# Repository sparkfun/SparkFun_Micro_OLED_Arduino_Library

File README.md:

SparkFun Micro OLED Breakout Arduino Library
========================================

<table class="table table-hover table-striped table-bordered">
  <tr align="center">
   <td></td>
   <td></td>
  </tr>
  <tr align="center">
    <td><i><a href="https://www.sparkfun.com/products/13003">SparkFun Micro OLED Breakout (LCD-13003)</a></i></td>
    <td><i><a href="https://www.sparkfun.com/products/14532">SparkFun Micro OLED Breakout (Qwiic)</a></i></td>
  </tr>
</table>

An Arduino library that allows you to draw shapes and text on the Micro OLED display and Qwiic micro OLED breakout.

Repository Contents
-------------------

* **/examples** - Example sketches for the library (.ino). Run these from the Arduino IDE.
* **/src** - Source files for the library (.cpp, .h).
* **keywords.txt** - Keywords from this library that will be highlighted in the Arduino IDE.
* **library.properties** - General library properties for the Arduino package manager.

Documentation
--------------

* **[Installing an Arduino Library Guide](https://learn.sparkfun.com/tutorials/installing-an-arduino-library)** - Basic information on how to install an Arduino library.
* **[Product Repository](https://github.com/sparkfun/Micro_OLED_Breakout)** - Main repository (including hardware files) for the Micro OLED Breakout.
* **[Hookup Guide](https://learn.sparkfun.com/tutorials/micro-oled-breakout-hookup-guide)** - Hookup guide for the Micro OLED Breakout.
* **[Hookup Guide (Qwiic version)](https://learn.sparkfun.com/tutorials/718)** - Hookup guide for the Micro OLED Breakout (Qwiic).

Products that use this Library
---------------------------------

* [Micro OLED Breakout](https://www.sparkfun.com/products/13003)- A breakout for the monochrome 64x48 OLED.
* [Micro OLED Breakout (Qwiic)](https://www.sparkfun.com/products/14532) - Qwiic version of the Micro OLED breakout with jumpers set for I2C

Contributing
--------------

If you would like to contribute to this library: please do, we truly appreciate it, but please follow [these guidelines](./CONTRIBUTING.md). Thanks!

MicroOLED: Version 1.3 - A New Hope
---------------

Prior to version 1.3, this library was hard-wired to the ```Wire``` I<sup>2</sup>C and ```SPI``` ports. Version 1.3
allows alternate ports to be used, in a way which is backward-compatible with the previous versions.

We have of course tested the new code, but if you do notice any compatibility issues please
[raise an issue](https://github.com/sparkfun/SparkFun_Micro_OLED_Arduino_Library/issues).

### I<sup>2</sup>C Example

Prior to v1.3, you would have used:
```
#define DC_JUMPER 1
MicroOLED oled(PIN_RESET, DC_JUMPER); // I2C declaration
```

followed by:
```
oled.begin();    // Initialize the OLED
```

From v1.3.0, you can still do it that way, or can do it like this:
```
MicroOLED oled(PIN_RESET); // The TwoWire I2C port is passed to .begin instead
```

followed by:
```
oled.begin(0x3D, Wire);    // Initialize the OLED using address 0x3D and the Wire port
```

To use a non-standard address or port, you can call:
```
oled.begin(0x3C, Qwiic);    // Initialize the OLED using address 0x3C and the Qwiic port
```

Please see [this example](./examples/Example10_MultiDemo_v13/Example10_MultiDemo_v13.ino) for more details.

### SPI Example

For SPI in v1.3, you still need to instantiate the oled using:
```
MicroOLED oled(PIN_RESET, PIN_DC, PIN_CS); //SPI declaration
```

If you want to use _SPI_ as the SPIClass, then you can continue to call:
```
  oled.begin();    // Initialize the OLED
```

To use a non-standard port, call:
```
  oled.begin(SPI1);    // Initialize the OLED using SPI1
```

Please see [this example](./examples/SPI/MicroOLED_Demo_v13/MicroOLED_Demo_v13.ino) for more details.

Version History
---------------

* [v 1.3.2](https://github.com/sparkfun/SparkFun_Micro_OLED_Arduino_Library/releases/tag/v1.3.2) - adds support for APOLLO3 v2, allow fonts to be included/excluded individually
* [v 1.3.0](https://github.com/sparkfun/SparkFun_Micro_OLED_Arduino_Library/releases/tag/v1.3.0) - adding support for non-standard I<sup>2</sup>C and SPI ports
* [v 1.2.10](https://github.com/sparkfun/SparkFun_Micro_OLED_Arduino_Library/releases/tag/v1.2.10) - prevent-write-outside-buffer corrections; improved I2C transfer speeds; includes the missing scroll functions; ```line``` corrections; ```enableDebugging```.
* [v 1.2.9](https://github.com/sparkfun/SparkFun_Micro_OLED_Arduino_Library/releases/tag/v1.2.9) - drawIcon() correction
* [v 1.2.8](https://github.com/sparkfun/SparkFun_Micro_OLED_Arduino_Library/releases/tag/v1%2C2.8) - Add drawIcon() and resort examples with Qwiic as default.
* [v 1.2.7](https://github.com/sparkfun/SparkFun_Micro_OLED_Arduino_Library/releases/tag/v1.2.7) - Add more comments and Wire.begin() to examples
* [v 1.2.6](https://github.com/sparkfun/SparkFun_Micro_OLED_Arduino_Library/releases/tag/V_1.2.6) - Removes call of Wire.begin from library
* [v 1.2.5](https://github.com/sparkfun/SparkFun_Micro_OLED_Arduino_Library/releases/tag/v1.2.5) - Adding Qwiic Examples for I2C
* [v 1.2.4](https://github.com/sparkfun/SparkFun_Micro_OLED_Arduino_Library/releases/tag/v.1.2.4) - Add colon to 7-segment font, add version history information to README, move and rename swap function to avoid namespace issues, add support for Arduino 101.
* [v 1.2.3](https://github.com/sparkfun/SparkFun_Micro_OLED_Arduino_Library/releases/tag/v1.2.3) -- Fix for I2C dcPin not configured
* [v 1.2.0](https://github.com/sparkfun/SparkFun_Micro_OLED_Arduino_Library/releases/tag/V_1.2.0) - add SAMD21 support, fix PROGMEM and `_BV` errors
* v 1.1.3 (not released)
* [v 1.1.2](https://github.com/sparkfun/SparkFun_Micro_OLED_Arduino_Library/tree/V_1.1.2) - Added compatibility for ESP8266
* [v 1.1.1](https://github.com/sparkfun/SparkFun_Micro_OLED_Arduino_Library/tree/V_1.1.1) - Changed to remove register level pin access, for cross-platform compatibility
* [v 1.1.0](https://github.com/sparkfun/SparkFun_Micro_OLED_Arduino_Library/tree/V_1.1.0) - Matching 1.6 standard
* [V 1.0.0](https://github.com/sparkfun/SparkFun_Micro_OLED_Arduino_Library/tree/V_1.0.0) - Initial release

License Information
-------------------

This product is _**open source**_!

Please see [LICENSE.md](./LICENSE.md) for more information.

Distributed as-is; no warranty is given.

- Your friends at SparkFun.

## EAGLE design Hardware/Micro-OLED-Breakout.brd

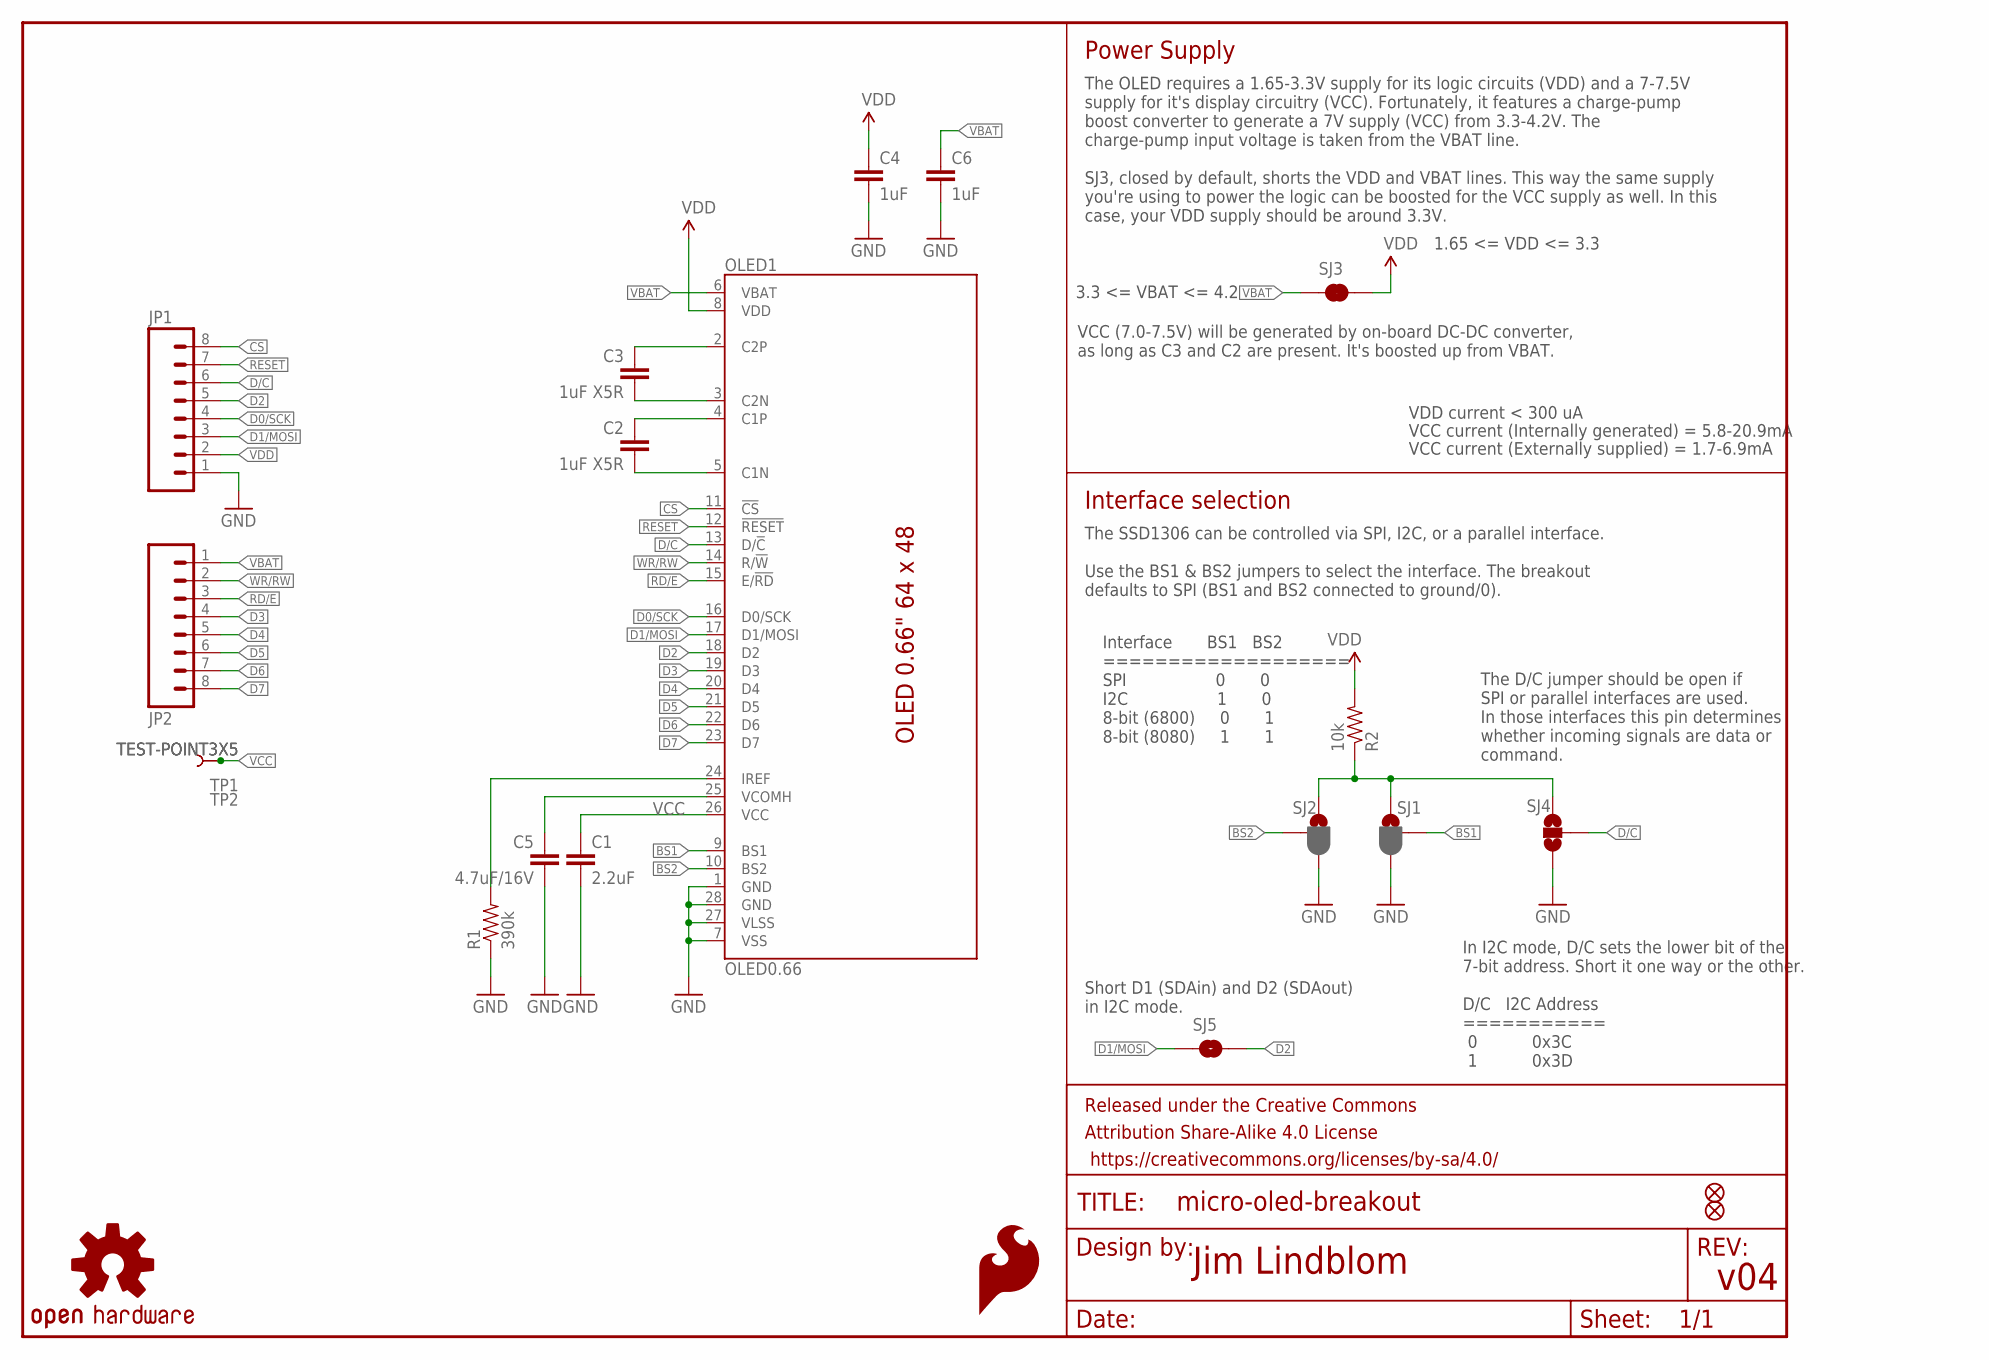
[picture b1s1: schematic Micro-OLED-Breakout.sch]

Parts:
C1: 2.2uF; 0805
C2, C3: 1uF X5R; 0805
C4, C6: 1uF; 0603-CAP
C5: 4.7uF/16V; 1206
FID1, FID2: FIDUCIAL1X2; FIDUCIAL-1X2
FRAME1: FRAME-LETTER; CREATIVE_COMMONS
JP1, JP2: M08; 1X08_PIN1_NO_SILK
LOGO3: OSHW-LOGOS; OSHW-LOGO-S
LOGO4: SFE_LOGO_FLAME.1_INCH; SFE_LOGO_FLAME_.1
OLED1: OLED0.66; OLED-0.66-64X48
R1: 390k; 0603-RES
R2: 10k; 0603-RES
SJ1: BS1; PAD-JUMPER-3-2OF3_NC_BY_PASTE_YES_SILK_FULL_BOX
SJ2: BS2; PAD-JUMPER-3-2OF3_NC_BY_PASTE_YES_SILK_FULL_BOX
SJ3: JUMPER-PAD-2-NC_BY_TRACENO_SILK; PAD-JUMPER-2-NC_BY_TRACE_NO_SILK
SJ4: JUMPER-PAD-3-NOTIGHT; PAD-JUMPER-3-NO-TIGHT
SJ5: JUMPER-PAD-2-NOYES_SILK; PAD-JUMPER-2-NO_YES_SILK
TP1, TP2: TEST-POINT3X5; PAD.03X.05

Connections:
BS1: OLED1.9 (BS1), SJ1.2
BS2: OLED1.10 (BS2), SJ2.2
C1N: C2.2, OLED1.5 (C1N)
C1P: C2.1, OLED1.4 (C1P)
C2N: C3.2, OLED1.3 (C2N)
C2P: C3.1, OLED1.2 (C2P)
CS: JP1.8, OLED1.11 (!CS!)
D0/SCK: JP1.4, OLED1.16 (D0/SCK)
D1/MOSI: JP1.3, OLED1.17 (D1/MOSI), SJ5.1
D2: JP1.5, OLED1.18 (D2), SJ5.2
D3: JP2.4, OLED1.19 (D3)
D4: JP2.5, OLED1.20 (D4)
D5: JP2.6, OLED1.21 (D5)
D6: JP2.7, OLED1.22 (D6)
D7: JP2.8, OLED1.23 (D7)
D/C: JP1.6, OLED1.13 (D/!C!), SJ4.2
GND: C1.2, C4.2, C5.2, C6.2, JP1.1, OLED1.1 (GND), OLED1.7 (VSS), OLED1.27 (VLSS), OLED1.28 (GND), R1.1, SJ1.3, SJ2.3, SJ4.3
IREF: OLED1.24 (IREF), R1.2
RD/E: JP2.3, OLED1.15 (E/!RD!)
RESET: JP1.7, OLED1.12 (!RESET!)
VBAT: C6.1, JP2.1, OLED1.6 (VBAT), SJ3.1
VCC: C1.1, OLED1.26 (VCC), TP1.P$1, TP2.P$1
VCOMH: C5.1, OLED1.25 (VCOMH)
VDD: C4.1, JP1.2, OLED1.8 (VDD), R2.2, SJ3.2
VDD_PU: R2.1, SJ1.1, SJ2.1, SJ4.1
WR/RW: JP2.2, OLED1.14 (R/!W!)

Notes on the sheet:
v04
Jim Lindblom
1.65 <= VDD <= 3.3
VDD current < 300 uA
VCC current (Internally generated) = 5.8-20.9mA
VCC current (Externally supplied) = 1.7-6.9mA
Interface BS1 BS2 =================== SPI 0 0 I2C 1 0 8-bit (6800) 0 1 8-bit (8080) 1 1
VCC (7.0-7.5V) will be generated by on-board DC-DC converter, as long as C3 and C2 are present. It's boosted up from VBAT.
3.3 <= VBAT <= 4.2
Interface selection
Short D1 (SDAin) and D2 (SDAout) in I2C mode.
The SSD1306 can be controlled via SPI, I2C, or a parallel interface. Use the BS1 & BS2 jumpers to select the interface. The breakout defaults to SPI (BS1 and BS2 connected to ground/0).
In I2C mode, D/C sets the lower bit of the 7-bit address. Short it one way or the other. D/C I2C Address =========== 0 0x3C 1 0x3D
Power Supply
The OLED requires a 1.65-3.3V supply for its logic circuits (VDD) and a 7-7.5V supply for it's display circuitry (VCC). Fortunately, it features a charge-pump boost converter to generate a 7V supply (VCC) from 3.3-4.2V. The charge-pump input voltage is taken from the VBAT line. SJ3, closed by defau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
The D/C jumper should be open if SPI or parallel interfaces are used. In those interfaces this pin determines whether incoming signals are data or command.

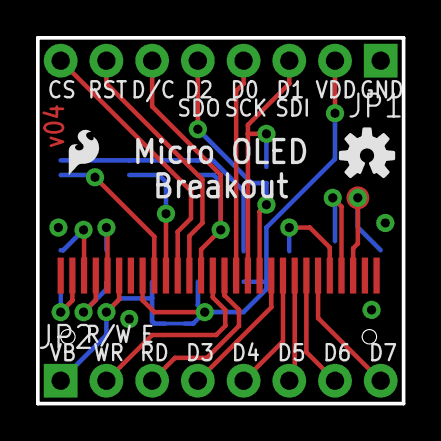
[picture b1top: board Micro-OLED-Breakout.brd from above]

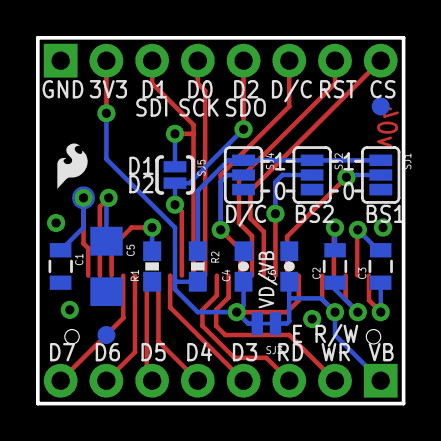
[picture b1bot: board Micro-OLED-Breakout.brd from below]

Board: 2 copper layers, 20.3 x 20.3 mm, 24 parts (17 on the bottom side), 26 nets.

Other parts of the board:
LOGO2: SFE_LOGO_FLAME.1_INCH; SFE_LOGO_FLAME_.1

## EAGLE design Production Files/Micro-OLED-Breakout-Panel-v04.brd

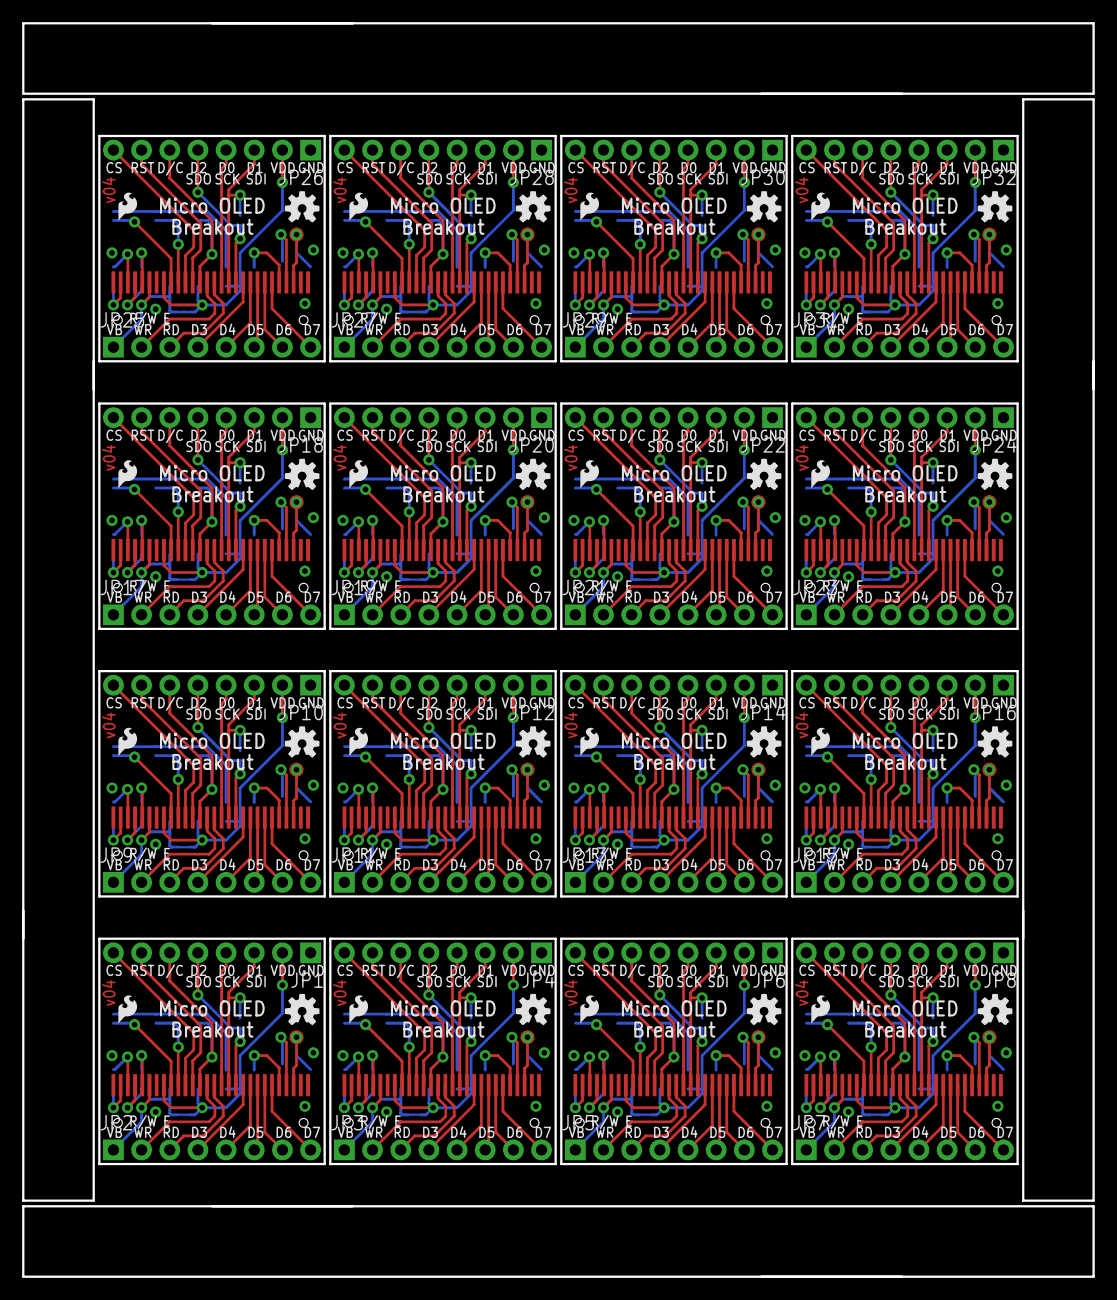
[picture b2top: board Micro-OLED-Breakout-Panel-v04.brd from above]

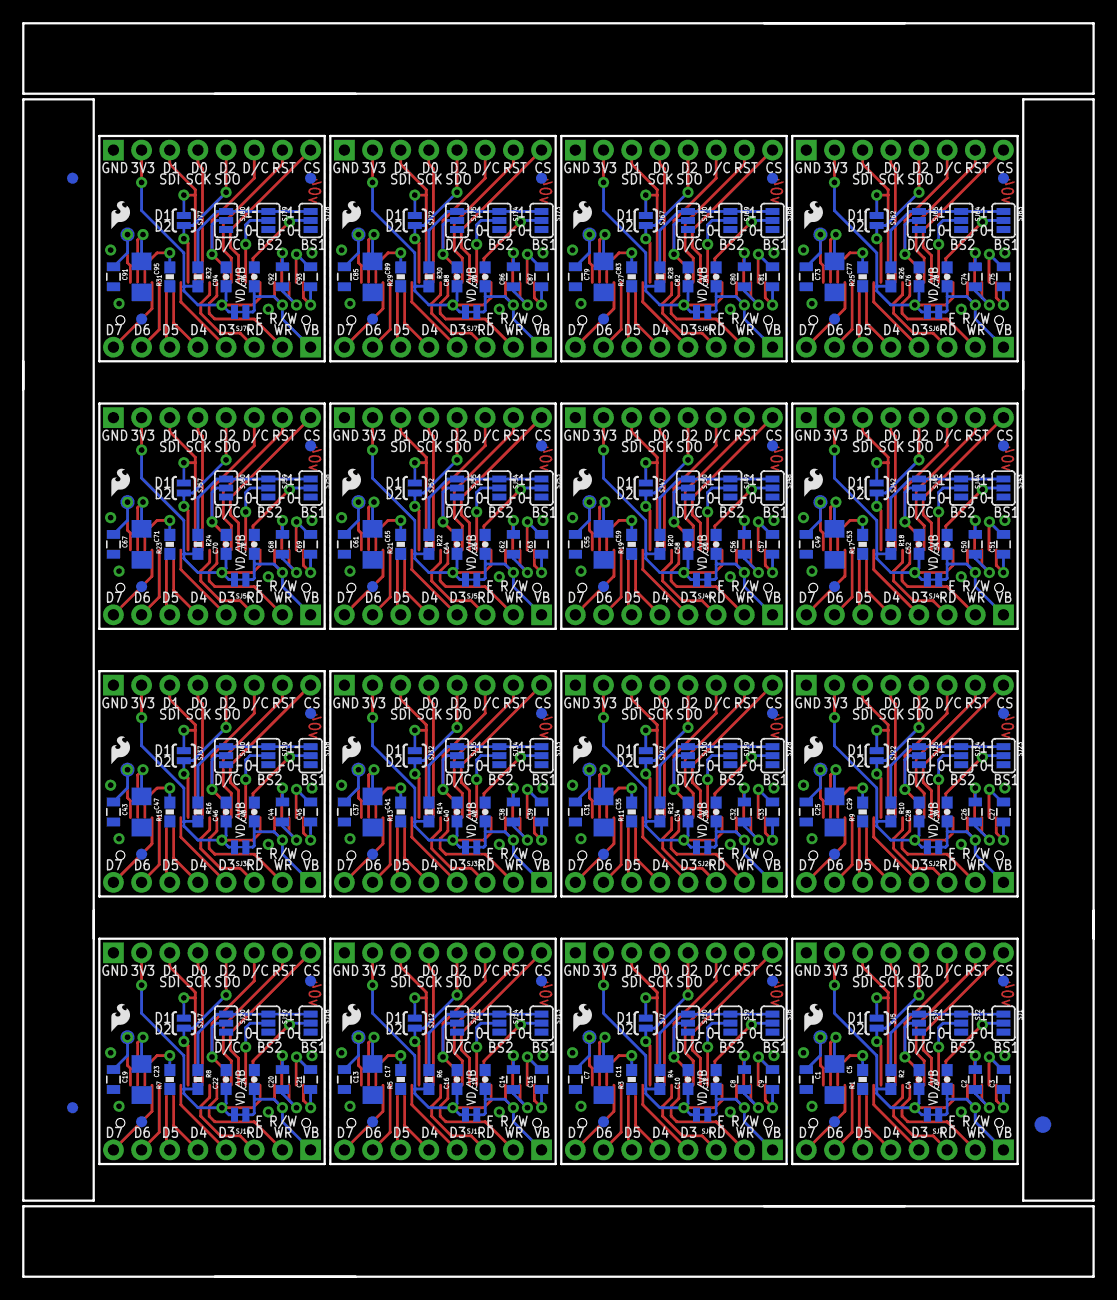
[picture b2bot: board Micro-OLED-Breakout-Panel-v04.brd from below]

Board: 2 copper layers, 96.5 x 113.0 mm, 371 parts (275 on the bottom side), 416 nets.

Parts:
C1, C7, C13, C19, C25, C31, C37, C43, C49, C55, C61, C67, C73, C79, C85, C91: 2.2uF; 0805
C2, C3, C8, C9, C14, C15, C20, C21, C26, C27, C32, C33, C38, C39, C44, C45, C50, C51, C56, C57, C62, C63, C68, C69, C74, C75, C80, C81, C86, C87, C92, C93: 1uF X5R; 0805
C4, C6, C10, C12, C16, C18, C22, C24, C28, C30, C34, C36, C40, C42, C46, C48, C52, C54, C58, C60, C64, C66, C70, C72, C76, C78, C82, C84, C88, C90, C94, C96: 1uF; 0603-CAP
C5, C11, C17, C23, C29, C35, C41, C47, C53, C59, C65, C71, C77, C83, C89, C95: 4.7uF/16V; 1206
E$1: FIDUCIAL-1.5X3
E$4, E$8: FIDUCIAL-1X2
FID1, FID2, FID3, FID4, FID5, FID6, FID7, FID8, FID9, FID10, FID11, FID12, FID13, FID14, FID15, FID16, FID17, FID18, FID19, FID20, FID21, FID22, FID23, FID24, FID25, FID26, FID27, FID28, FID29, FID30, FID31, FID32: FIDUCIAL1X2; FIDUCIAL-1X2
JP1, JP2, JP3, JP4, JP5, JP6, JP7, JP8, JP9, JP10, JP11, JP12, JP13, JP14, JP15, JP16, JP17, JP18, JP19, JP20, JP21, JP22, JP23, JP24, JP25, JP26, JP27, JP28, JP29, JP30, JP31, JP32: 1X08_PIN1_NO_SILK
LOGO1, LOGO2, LOGO4, LOGO5, LOGO7, LOGO8, LOGO10, LOGO11, LOGO13, LOGO14, LOGO16, LOGO17, LOGO19, LOGO20, LOGO22, LOGO23, LOGO25, LOGO26, LOGO28, LOGO29, LOGO31, LOGO32, LOGO34, LOGO35, LOGO37, LOGO38, LOGO40, LOGO41, LOGO43, LOGO44, LOGO46, LOGO47: SFE_LOGO_FLAME.1_INCH; SFE_LOGO_FLAME_.1
LOGO3, LOGO6, LOGO9, LOGO12, LOGO15, LOGO18, LOGO21, LOGO24, LOGO27, LOGO30, LOGO33, LOGO36, LOGO39, LOGO42, LOGO45, LOGO48: OSHW-LOGOS; OSHW-LOGO-S
OLED1, OLED2, OLED3, OLED4, OLED5, OLED6, OLED7, OLED8, OLED9, OLED10, OLED11, OLED12, OLED13, OLED14, OLED15, OLED16: OLED0.66; OLED-0.66-64X48
R1, R3, R5, R7, R9, R11, R13, R15, R17, R19, R21, R23, R25, R27, R29, R31: 390k; 0603-RES
R2, R4, R6, R8, R10, R12, R14, R16, R18, R20, R22, R24, R26, R28, R30, R32: 10k; 0603-RES
SJ1, SJ8, SJ13, SJ18, SJ23, SJ28, SJ33, SJ38, SJ43, SJ48, SJ53, SJ58, SJ63, SJ68, SJ73, SJ78: BS1; PAD-JUMPER-3-2OF3_NC_BY_PASTE_YES_SILK_FULL_BOX
SJ2, SJ9, SJ14, SJ19, SJ24, SJ29, SJ34, SJ39, SJ44, SJ49, SJ54, SJ59, SJ64, SJ69, SJ74, SJ79: BS2; PAD-JUMPER-3-2OF3_NC_BY_PASTE_YES_SILK_FULL_BOX
SJ3, SJ6, SJ11, SJ16, SJ21, SJ26, SJ31, SJ36, SJ41, SJ46, SJ51, SJ56, SJ61, SJ66, SJ71, SJ76: PAD-JUMPER-2-NC_BY_TRACE_NO_SILK
SJ4, SJ10, SJ15, SJ20, SJ25, SJ30, SJ35, SJ40, SJ45, SJ50, SJ55, SJ60, SJ65, SJ70, SJ75, SJ80: PAD-JUMPER-3-NO-TIGHT
SJ5, SJ7, SJ12, SJ17, SJ22, SJ27, SJ32, SJ37, SJ42, SJ47, SJ52, SJ57, SJ62, SJ67, SJ72, SJ77: PAD-JUMPER-2-NO_YES_SILK
TP1, TP2, TP3, TP4, TP5, TP6, TP7, TP8, TP9, TP10, TP11, TP12, TP13, TP14, TP15, TP16, TP17, TP18, TP19, TP20, TP21, TP22, TP23, TP24, TP25, TP26, TP27, TP28, TP29, TP30, TP31, TP32: TEST-POINT3X5; PAD.03X.05

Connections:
BS1: OLED1.9, SJ1.2
BS2: OLED1.10, SJ2.2
BS3: OLED2.9, SJ8.2
BS4: OLED2.10, SJ9.2
BS5: OLED3.9, SJ13.2
BS6: OLED3.10, SJ14.2
BS7: OLED4.9, SJ18.2
BS8: OLED4.10, SJ19.2
BS9: OLED5.9, SJ23.2
BS10: OLED5.10, SJ24.2
BS11: OLED6.9, SJ28.2
BS12: OLED6.10, SJ29.2
BS13: OLED7.9, SJ33.2
BS14: OLED7.10, SJ34.2
BS15: OLED8.9, SJ38.2
BS16: OLED8.10, SJ39.2
BS17: OLED9.9, SJ43.2
BS18: OLED9.10, SJ44.2
BS19: OLED10.9, SJ48.2
BS20: OLED10.10, SJ49.2
BS21: OLED11.9, SJ53.2
BS22: OLED11.10, SJ54.2
BS23: OLED12.9, SJ58.2
BS24: OLED12.10, SJ59.2
BS25: OLED13.9, SJ63.2
BS26: OLED13.10, SJ64.2
BS27: OLED14.9, SJ68.2
BS28: OLED14.10, SJ69.2
BS29: OLED15.9, SJ73.2
BS30: OLED15.10, SJ74.2
BS31: OLED16.9, SJ78.2
BS32: OLED16.10, SJ79.2
C1N: C2.2, OLED1.5
C1N1: C8.2, OLED2.5
C1N2: C14.2, OLED3.5
C1N3: C20.2, OLED4.5
C1N4: C26.2, OLED5.5
C1N5: C32.2, OLED6.5
C1N6: C38.2, OLED7.5
C1N7: C44.2, OLED8.5
C1N8: C50.2, OLED9.5
C1N9: C56.2, OLED10.5
C1N10: C62.2, OLED11.5
C1N11: C68.2, OLED12.5
C1N12: C74.2, OLED13.5
C1N13: C80.2, OLED14.5
C1N14: C86.2, OLED15.5
C1N15: C92.2, OLED16.5
C1P: C2.1, OLED1.4
C1P1: C8.1, OLED2.4
C1P2: C14.1, OLED3.4
C1P3: C20.1, OLED4.4
C1P4: C26.1, OLED5.4
C1P5: C32.1, OLED6.4
C1P6: C38.1, OLED7.4
C1P7: C44.1, OLED8.4
C1P8: C50.1, OLED9.4
C1P9: C56.1, OLED10.4
C1P10: C62.1, OLED11.4
C1P11: C68.1, OLED12.4
C1P12: C74.1, OLED13.4
C1P13: C80.1, OLED14.4
C1P14: C86.1, OLED15.4
C1P15: C92.1, OLED16.4
C2N: C3.2, OLED1.3
C2N1: C9.2, OLED2.3
C2N2: C15.2, OLED3.3
C2N3: C21.2, OLED4.3
C2N4: C27.2, OLED5.3
C2N5: C33.2, OLED6.3
C2N6: C39.2, OLED7.3
C2N7: C45.2, OLED8.3
C2N8: C51.2, OLED9.3
C2N9: C57.2, OLED10.3
C2N10: C63.2, OLED11.3
C2N11: C69.2, OLED12.3
C2N12: C75.2, OLED13.3
C2N13: C81.2, OLED14.3
C2N14: C87.2, OLED15.3
C2N15: C93.2, OLED16.3
C2P: C3.1, OLED1.2
C2P1: C9.1, OLED2.2
C2P2: C15.1, OLED3.2
C2P3: C21.1, OLED4.2
C2P4: C27.1, OLED5.2
C2P5: C33.1, OLED6.2
C2P6: C39.1, OLED7.2
C2P7: C45.1, OLED8.2
C2P8: C51.1, OLED9.2
C2P9: C57.1, OLED10.2
C2P10: C63.1, OLED11.2
C2P11: C69.1, OLED12.2
C2P12: C75.1, OLED13.2
C2P13: C81.1, OLED14.2
C2P14: C87.1, OLED15.2
C2P15: C93.1, OLED16.2
CS: JP1.8, OLED1.11
CS1: JP4.8, OLED2.11
CS2: JP6.8, OLED3.11
CS3: JP8.8, OLED4.11
CS4: JP10.8, OLED5.11
CS5: JP12.8, OLED6.11
CS6: JP14.8, OLED7.11
CS7: JP16.8, OLED8.11
CS8: JP18.8, OLED9.11
CS9: JP20.8, OLED10.11
CS10: JP22.8, OLED11.11
CS11: JP24.8, OLED12.11
CS12: JP26.8, OLED13.11
CS13: JP28.8, OLED14.11
CS14: JP30.8, OLED15.11
CS15: JP32.8, OLED16.11
D0/SCK: JP1.4, OLED1.16
D0/SCK1: JP4.4, OLED2.16
D0/SCK2: JP6.4, OLED3.16
D0/SCK3: JP8.4, OLED4.16
D0/SCK4: JP10.4, OLED5.16
D0/SCK5: JP12.4, OLED6.16
D0/SCK6: JP14.4, OLED7.16
D0/SCK7: JP16.4, OLED8.16
D0/SCK8: JP18.4, OLED9.16
D0/SCK9: JP20.4, OLED10.16
D0/SCK10: JP22.4, OLED11.16
D0/SCK11: JP24.4, OLED12.16
D0/SCK12: JP26.4, OLED13.16
D0/SCK13: JP28.4, OLED14.16
D0/SCK14: JP30.4, OLED15.16
D0/SCK15: JP32.4, OLED16.16
D1: JP3.8, OLED2.23
D1/MOSI: JP1.3, OLED1.17, SJ5.1
D1/MOSI1: JP4.3, OLED2.17, SJ7.1
D1/MOSI2: JP6.3, OLED3.17, SJ12.1
D1/MOSI3: JP8.3, OLED4.17, SJ17.1
D1/MOSI4: JP10.3, OLED5.17, SJ22.1
D1/MOSI5: JP12.3, OLED6.17, SJ27.1
D1/MOSI6: JP14.3, OLED7.17, SJ32.1
D1/MOSI7: JP16.3, OLED8.17, SJ37.1
D1/MOSI8: JP18.3, OLED9.17, SJ42.1
D1/MOSI9: JP20.3, OLED10.17, SJ47.1
D1/MOSI10: JP22.3, OLED11.17, SJ52.1
D1/MOSI11: JP24.3, OLED12.17, SJ57.1
D1/MOSI12: JP26.3, OLED13.17, SJ62.1
D1/MOSI13: JP28.3, OLED14.17, SJ67.1
D1/MOSI14: JP30.3, OLED15.17, SJ72.1
D1/MOSI15: JP32.3, OLED16.17, SJ77.1
D2: JP1.5, OLED1.18, SJ5.2
D3: JP2.4, OLED1.19
D4: JP2.5, OLED1.20
D5: JP2.6, OLED1.21
D6: JP2.7, OLED1.22
D7: JP2.8, OLED1.23
D8: JP3.7, OLED2.22
D9: JP3.6, OLED2.21
D10: JP3.5, OLED2.20
D11: JP3.4, OLED2.19
D12: JP4.5, OLED2.18, SJ7.2
D13: JP5.8, OLED3.23
D14: JP5.7, OLED3.22
D15: JP5.6, OLED3.21
D16: JP5.5, OLED3.20
D17: JP5.4, OLED3.19
D18: JP6.5, OLED3.18, SJ12.2
D19: JP7.8, OLED4.23
D20: JP7.7, OLED4.22
D21: JP7.6, OLED4.21
D22: JP7.5, OLED4.20
D23: JP7.4, OLED4.19
D24: JP8.5, OLED4.18, SJ17.2
D25: JP9.8, OLED5.23
D26: JP9.7, OLED5.22
D27: JP9.6, OLED5.21
D28: JP9.5, OLED5.20
D29: JP9.4, OLED5.19
D30: JP10.5, OLED5.18, SJ22.2
D31: JP11.8, OLED6.23
D32: JP11.7, OLED6.22
D33: JP11.6, OLED6.21
D34: JP11.5, OLED6.20
D35: JP11.4, OLED6.19
D36: JP12.5, OLED6.18, SJ27.2
D37: JP13.8, OLED7.23
D38: JP13.7, OLED7.22
D39: JP13.6, OLED7.21
D40: JP13.5, OLED7.20
D41: JP13.4, OLED7.19
D42: JP14.5, OLED7.18, SJ32.2
D43: JP15.8, OLED8.23
D44: JP15.7, OLED8.22
D45: JP15.6, OLED8.21
D46: JP15.5, OLED8.20
D47: JP15.4, OLED8.19
D48: JP16.5, OLED8.18, SJ37.2
D49: JP17.8, OLED9.23
D50: JP17.7, OLED9.22
D51: JP17.6, OLED9.21
D52: JP17.5, OLED9.20
D53: JP17.4, OLED9.19
D54: JP18.5, OLED9.18, SJ42.2
D55: JP19.8, OLED10.23
D56: JP19.7, OLED10.22
D57: JP19.6, OLED10.21
D58: JP19.5, OLED10.20
D59: JP19.4, OLED10.19
D60: JP20.5, OLED10.18, SJ47.2
D61: JP21.8, OLED11.23
D62: JP21.7, OLED11.22
D63: JP21.6, OLED11.21
D64: JP21.5, OLED11.20
D65: JP21.4, OLED11.19
D66: JP22.5, OLED11.18, SJ52.2
D67: JP23.8, OLED12.23
D68: JP23.7, OLED12.22
D69: JP23.6, OLED12.21
D70: JP23.5, OLED12.20
D71: JP23.4, OLED12.19
D72: JP24.5, OLED12.18, SJ57.2
D73: JP25.8, OLED13.23
D74: JP25.7, OLED13.22
D75: JP25.6, OLED13.21
D76: JP25.5, OLED13.20
D77: JP25.4, OLED13.19
D78: JP26.5, OLED13.18, SJ62.2
D79: JP27.8, OLED14.23
D80: JP27.7, OLED14.22
D81: JP27.6, OLED14.21
D82: JP27.5, OLED14.20
D83: JP27.4, OLED14.19
D84: JP28.5, OLED14.18, SJ67.2
D85: JP29.8, OLED15.23
D86: JP29.7, OLED15.22
D87: JP29.6, OLED15.21
D88: JP29.5, OLED15.20
D89: JP29.4, OLED15.19
D90: JP30.5, OLED15.18, SJ72.2
D91: JP31.8, OLED16.23
D92: JP31.7, OLED16.22
D93: JP31.6, OLED16.21
D94: JP31.5, OLED16.20
D95: JP31.4, OLED16.19
D96: JP32.5, OLED16.18, SJ77.2
D/C: JP1.6, OLED1.13, SJ4.2
D/C1: JP4.6, OLED2.13, SJ10.2
D/C2: JP6.6, OLED3.13, SJ15.2
D/C3: JP8.6, OLED4.13, SJ20.2
D/C4: JP10.6, OLED5.13, SJ25.2
D/C5: JP12.6, OLED6.13, SJ30.2
D/C6: JP14.6, OLED7.13, SJ35.2
D/C7: JP16.6, OLED8.13, SJ40.2
D/C8: JP18.6, OLED9.13, SJ45.2
D/C9: JP20.6, OLED10.13, SJ50.2
D/C10: JP22.6, OLED11.13, SJ55.2
D/C11: JP24.6, OLED12.13, SJ60.2
D/C12: JP26.6, OLED13.13, SJ65.2
D/C13: JP28.6, OLED14.13, SJ70.2
D/C14: JP30.6, OLED15.13, SJ75.2
D/C15: JP32.6, OLED16.13, SJ80.2
GND: C1.2, C4.2, C5.2, C6.2, JP1.1, OLED1.1, OLED1.7, OLED1.27, OLED1.28, R1.1, SJ1.3, SJ2.3, SJ4.3
GND1: C7.2, C10.2, C11.2, C12.2, JP4.1, OLED2.1, OLED2.7, OLED2.27, OLED2.28, R3.1, SJ8.3, SJ9.3, SJ10.3
GND2: C13.2, C16.2, C17.2, C18.2, JP6.1, OLED3.1, OLED3.7, OLED3.27, OLED3.28, R5.1, SJ13.3, SJ14.3, SJ15.3
GND3: C19.2, C22.2, C23.2, C24.2, JP8.1, OLED4.1, OLED4.7, OLED4.27, OLED4.28, R7.1, SJ18.3, SJ19.3, SJ20.3
GND4: C25.2, C28.2, C29.2, C30.2, JP10.1, OLED5.1, OLED5.7, OLED5.27, OLED5.28, R9.1, SJ23.3, SJ24.3, SJ25.3
GND5: C31.2, C34.2, C35.2, C36.2, JP12.1, OLED6.1, OLED6.7, OLED6.27, OLED6.28, R11.1, SJ28.3, SJ29.3, SJ30.3
GND6: C37.2, C40.2, C41.2, C42.2, JP14.1, OLED7.1, OLED7.7, OLED7.27, OLED7.28, R13.1, SJ33.3, SJ34.3, SJ35.3
GND7: C43.2, C46.2, C47.2, C48.2, JP16.1, OLED8.1, OLED8.7, OLED8.27, OLED8.28, R15.1, SJ38.3, SJ39.3, SJ40.3
GND8: C49.2, C52.2, C53.2, C54.2, JP18.1, OLED9.1, OLED9.7, OLED9.27, OLED9.28, R17.1, SJ43.3, SJ44.3, SJ45.3
GND9: C55.2, C58.2, C59.2, C60.2, JP20.1, OLED10.1, OLED10.7, OLED10.27, OLED10.28, R19.1, SJ48.3, SJ49.3, SJ50.3
GND10: C61.2, C64.2, C65.2, C66.2, JP22.1, OLED11.1, OLED11.7, OLED11.27, OLED11.28, R21.1, SJ53.3, SJ54.3, SJ55.3
GND11: C67.2, C70.2, C71.2, C72.2, JP24.1, OLED12.1, OLED12.7, OLED12.27, OLED12.28, R23.1, SJ58.3, SJ59.3, SJ60.3
GND12: C73.2, C76.2, C77.2, C78.2, JP26.1, OLED13.1, OLED13.7, OLED13.27, OLED13.28, R25.1, SJ63.3, SJ64.3, SJ65.3
GND13: C79.2, C82.2, C83.2, C84.2, JP28.1, OLED14.1, OLED14.7, OLED14.27, OLED14.28, R27.1, SJ68.3, SJ69.3, SJ70.3
GND14: C85.2, C88.2, C89.2, C90.2, JP30.1, OLED15.1, OLED15.7, OLED15.27, OLED15.28, R29.1, SJ73.3, SJ74.3, SJ75.3
GND15: C91.2, C94.2, C95.2, C96.2, JP32.1, OLED16.1, OLED16.7, OLED16.27, OLED16.28, R31.1, SJ78.3, SJ79.3, SJ80.3
IREF: OLED1.24, R1.2
IREF1: OLED2.24, R3.2
IREF2: OLED3.24, R5.2
IREF3: OLED4.24, R7.2
IREF4: OLED5.24, R9.2
IREF5: OLED6.24, R11.2
IREF6: OLED7.24, R13.2
IREF7: OLED8.24, R15.2
IREF8: OLED9.24, R17.2
IREF9: OLED10.24, R19.2
IREF10: OLED11.24, R21.2
IREF11: OLED12.24, R23.2
IREF12: OLED13.24, R25.2
IREF13: OLED14.24, R27.2
IREF14: OLED15.24, R29.2
IREF15: OLED16.24, R31.2
RD/E: JP2.3, OLED1.15
RD/E1: JP3.3, OLED2.15
RD/E2: JP5.3, OLED3.15
RD/E3: JP7.3, OLED4.15
RD/E4: JP9.3, OLED5.15
RD/E5: JP11.3, OLED6.15
RD/E6: JP13.3, OLED7.15
RD/E7: JP15.3, OLED8.15
RD/E8: JP17.3, OLED9.15
RD/E9: JP19.3, OLED10.15
RD/E10: JP21.3, OLED11.15
RD/E11: JP23.3, OLED12.15
RD/E12: JP25.3, OLED13.15
RD/E13: JP27.3, OLED14.15
RD/E14: JP29.3, OLED15.15
RD/E15: JP31.3, OLED16.15
RESET: JP1.7, OLED1.12
RESET1: JP4.7, OLED2.12
RESET2: JP6.7, OLED3.12
RESET3: JP8.7, OLED4.12
RESET4: JP10.7, OLED5.12
RESET5: JP12.7, OLED6.12
RESET6: JP14.7, OLED7.12
RESET7: JP16.7, OLED8.12
RESET8: JP18.7, OLED9.12
RESET9: JP20.7, OLED10.12
RESET10: JP22.7, OLED11.12
RESET11: JP24.7, OLED12.12
RESET12: JP26.7, OLED13.12
RESET13: JP28.7, OLED14.12
RESET14: JP30.7, OLED15.12
RESET15: JP32.7, OLED16.12
VBAT: C6.1, JP2.1, OLED1.6, SJ3.1
VBAT1: C12.1, JP3.1, OLED2.6, SJ6.1
VBAT2: C18.1, JP5.1, OLED3.6, SJ11.1
VBAT3: C24.1, JP7.1, OLED4.6, SJ16.1
VBAT4: C30.1, JP9.1, OLED5.6, SJ21.1
VBAT5: C36.1, JP11.1, OLED6.6, SJ26.1
VBAT6: C42.1, JP13.1, OLED7.6, SJ31.1
VBAT7: C48.1, JP15.1, OLED8.6, SJ36.1
VBAT8: C54.1, JP17.1, OLED9.6, SJ41.1
VBAT9: C60.1, JP19.1, OLED10.6, SJ46.1
VBAT10: C66.1, JP21.1, OLED11.6, SJ51.1
VBAT11: C72.1, JP23.1, OLED12.6, SJ56.1
VBAT12: C78.1, JP25.1, OLED13.6, SJ61.1
VBAT13: C84.1, JP27.1, OLED14.6, SJ66.1
VBAT14: C90.1, JP29.1, OLED15.6, SJ71.1
VBAT15: C96.1, JP31.1, OLED16.6, SJ76.1
VCC: C1.1, OLED1.26, TP1.P$1, TP2.P$1
VCC1: C7.1, OLED2.26, TP3.P$1, TP4.P$1
VCC2: C13.1, OLED3.26, TP5.P$1, TP6.P$1
VCC3: C19.1, OLED4.26, TP7.P$1, TP8.P$1
VCC4: C25.1, OLED5.26, TP9.P$1, TP10.P$1
VCC5: C31.1, OLED6.26, TP11.P$1, TP12.P$1
VCC6: C37.1, OLED7.26, TP13.P$1, TP14.P$1
VCC7: C43.1, OLED8.26, TP15.P$1, TP16.P$1
VCC8: C49.1, OLED9.26, TP17.P$1, TP18.P$1
VCC9: C55.1, OLED10.26, TP19.P$1, TP20.P$1
VCC10: C61.1, OLED11.26, TP21.P$1, TP22.P$1
VCC11: C67.1, OLED12.26, TP23.P$1, TP24.P$1
VCC12: C73.1, OLED13.26, TP25.P$1, TP26.P$1
VCC13: C79.1, OLED14.26, TP27.P$1, TP28.P$1
VCC14: C85.1, OLED15.26, TP29.P$1, TP30.P$1
VCC15: C91.1, OLED16.26, TP31.P$1, TP32.P$1
VCOMH: C5.1, OLED1.25
VCOMH1: C11.1, OLED2.25
VCOMH2: C17.1, OLED3.25
VCOMH3: C23.1, OLED4.25
VCOMH4: C29.1, OLED5.25
VCOMH5: C35.1, OLED6.25
VCOMH6: C41.1, OLED7.25
VCOMH7: C47.1, OLED8.25
VCOMH8: C53.1, OLED9.25
VCOMH9: C59.1, OLED10.25
VCOMH10: C65.1, OLED11.25
VCOMH11: C71.1, OLED12.25
VCOMH12: C77.1, OLED13.25
VCOMH13: C83.1, OLED14.25
VCOMH14: C89.1, OLED15.25
VCOMH15: C95.1, OLED16.25
VDD: C4.1, JP1.2, OLED1.8, R2.2, SJ3.2
VDD1: C10.1, JP4.2, OLED2.8, R4.2, SJ6.2
VDD2: C16.1, JP6.2, OLED3.8, R6.2, SJ11.2
VDD3: C22.1, JP8.2, OLED4.8, R8.2, SJ16.2
VDD4: C28.1, JP10.2, OLED5.8, R10.2, SJ21.2
VDD5: C34.1, JP12.2, OLED6.8, R12.2, SJ26.2
VDD6: C40.1, JP14.2, OLED7.8, R14.2, SJ31.2
VDD7: C46.1, JP16.2, OLED8.8, R16.2, SJ36.2
VDD8: C52.1, JP18.2, OLED9.8, R18.2, SJ41.2
VDD9: C58.1, JP20.2, OLED10.8, R20.2, SJ46.2
VDD10: C64.1, JP22.2, OLED11.8, R22.2, SJ51.2
VDD11: C70.1, JP24.2, OLED12.8, R24.2, SJ56.2
VDD12: C76.1, JP26.2, OLED13.8, R26.2, SJ61.2
VDD13: C82.1, JP28.2, OLED14.8, R28.2, SJ66.2
VDD14: C88.1, JP30.2, OLED15.8, R30.2, SJ71.2
VDD15: C94.1, JP32.2, OLED16.8, R32.2, SJ76.2
VDD_PU: R2.1, SJ1.1, SJ2.1, SJ4.1
VDD_PU1: R4.1, SJ8.1, SJ9.1, SJ10.1
VDD_PU2: R6.1, SJ13.1, SJ14.1, SJ15.1
VDD_PU3: R8.1, SJ18.1, SJ19.1, SJ20.1
VDD_PU4: R10.1, SJ23.1, SJ24.1, SJ25.1
VDD_PU5: R12.1, SJ28.1, SJ29.1, SJ30.1
VDD_PU6: R14.1, SJ33.1, SJ34.1, SJ35.1
VDD_PU7: R16.1, SJ38.1, SJ39.1, SJ40.1
VDD_PU8: R18.1, SJ43.1, SJ44.1, SJ45.1
VDD_PU9: R20.1, SJ48.1, SJ49.1, SJ50.1
VDD_PU10: R22.1, SJ53.1, SJ54.1, SJ55.1
VDD_PU11: R24.1, SJ58.1, SJ59.1, SJ60.1
VDD_PU12: R26.1, SJ63.1, SJ64.1, SJ65.1
VDD_PU13: R28.1, SJ68.1, SJ69.1, SJ70.1
VDD_PU14: R30.1, SJ73.1, SJ74.1, SJ75.1
VDD_PU15: R32.1, SJ78.1, SJ79.1, SJ80.1
WR/RW: JP2.2, OLED1.14
WR/RW1: JP3.2, OLED2.14
WR/RW2: JP5.2, OLED3.14
WR/RW3: JP7.2, OLED4.14
WR/RW4: JP9.2, OLED5.14
WR/RW5: JP11.2, OLED6.14
WR/RW6: JP13.2, OLED7.14
WR/RW7: JP15.2, OLED8.14
WR/RW8: JP17.2, OLED9.14
WR/RW9: JP19.2, OLED10.14
WR/RW10: JP21.2, OLED11.14
WR/RW11: JP23.2, OLED12.14
WR/RW12: JP25.2, OLED13.14
WR/RW13: JP27.2, OLED14.14
WR/RW14: JP29.2, OLED15.14
WR/RW15: JP31.2, OLED16.14

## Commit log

2014-06-30 Initial commit of hardware (v01)
2014-06-30 Revising board shape, OLED (v02)
2014-07-23 Fixing swapped BS1 and BS2 labels (v03)
2014-07-28 Adding D/C jumper (open by default) (v04)
    Allows address selection in I2C mode.
    Also:
    * adding some notes to schematic
    * Shuffling around silk labels. Avoiding holes.
2014-07-30 Couple minor silk, via placement adjustments (v04)
2014-08-05 created panel v04
2014-09-07 initial commit of Arduino library
2014-10-28 Massive overhaul of Arduino library. Fixed constructors. New exampeles.
2015-01-20 Added drawBitmap function to library
    Added drawBitmap function to library as well as an example in the
    examples folder. Also added getScreenBuffer function from the MicroView
    library to this library.
2015-04-24 Revising structure to match 1.6 standard.
2015-04-24 Fixing README.md image
2015-04-28 Modified for platform agnosticism - original code used pointers to registers in the AVR arch to speed read/write pin access. Changed that to normal digitalWrite digitalRead functions to allow the cod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
2015-04-28 Updating library.properties
2015-05-01 Update README.md
    Removing reference to extras in readme.
2015-07-27 Modified library to detect the microcontroller used and to add the pgmspace header file accordingly
2015-07-27 Modified the library properties to be same as that of the original sparkfun file
2015-07-27 Modified Comment
2015-07-27 Updating README with new version history
2015-07-27 Updating library.properties to 1.1.2
2015-08-13 Add font #4 'fontlargeletter31x48'
2015-08-17 Bumping TOTALFONTS up to 5
2015-08-17 Fixing character count in fontlargeletter31x48
2015-08-17 Adding flag to disable fontlargeletter by default.
    The 31x48 font uses a large amount of memory - about 7k. Uncommenting out
    the `#define INCLUDE_LARGE_LETTER_FONT` line, near the top of
    SFE_MicroOLED.cpp will enable the font.
2015-10-18 Load <avr/pgmspace.h> for Teensy3
2015-10-20 Adding catch if _BV isn't defined
2015-10-20 Upping version number
2016-04-21 remove PROGMEM
2016-04-21 conditionnal PROGMEM
2016-07-26 add json information for platformio
2016-07-26 Use original SparkFun repo
2016-08-20 update flags to detect ESP8266
2016-09-15 SAMD21 support - fixing SAMD21 SPI support and PROGMEM errors.
2017-05-16 Add Support for Arduino 101
    Add support for Arduino 101 by loading <avr/pgmspace.h> using the
    __ARDUINO_ARC__ variable defined in the Arduino 101 platform
    definition file.
2017-05-20 Added a ':' to the 7segment font!
2017-06-28 Change swap def to swapOLED, to avoid problems with some platforms
2017-11-13 add missing versions to version history
    I tried to read the commits, I may have gotten something wrong.
2018-06-10 Fix issue 19 and lib ver roll.
2018-06-11 Moving dcPin init to SPI and parallel setup functions
2018-06-11 Lib ver roll
2018-06-14 remove mismatched bracket
2018-06-25 Adding version history information.
2018-06-25 Moving swapOLED to cpp.
2018-06-25 Incrementing library version.
2018-12-04 adding qwiic examples
2018-12-04 previous version didn't have library properties rolled, rolling properties
2018-12-04 rolling json version number
2018-12-18 remove wire.begin from library
2019-03-08 Use 'getFontHeight'
2019-06-02 initialize Wire lib in I2C setup
2019-06-10 Add Comment and Wire.begin()
    - Add Wire.begin() to the setup() in the examples since it was removed from the .cpp file.
    - Adding comments to clarify on when to use certain functions for SPI and I2C
2019-06-10 Update Comments
    - Update comments for DC_JUMPER (not significant enough to warrant change in library version number).
2020-10-09 Update MicroOLED_Clock.ino
    this is not the cube example
2020-11-14 VSC whitespace change
2020-11-16 Add drawIcon() and example
2020-11-16 Re-sort examples. Make primary examples I2C with SPI sub folder.
2020-11-16 Update readme and library properties.
2020-11-21 Fix icon size typo.
2020-12-09 Prevent writes outside buffer
2020-12-09 Remove unused define.
2020-12-10 Adding i2cWriteMultiple to speed up I2C transfers
2020-12-10 Removing unnecessary 'memcpy'
2020-12-10 Adding the missing scroll functions (work in progress)
2020-12-10 Added the missing scroll functions. Added scrollInterval as a parameter.
2020-12-10 Adding the scroll example
2020-12-10 Removing the (dead) link to microview.io
2020-12-10 Changing the default I2C address for Example8
2020-12-11 Adding enableDebugging. Corrected line (missing last pixel)
2020-12-11 Adding Example9_Lines. Illustrates correct line functionality
2020-12-11 Updating Example9: changing the default I2C address; disabling debug prints.
2020-12-11 Adding CONTRIBUTING
2020-12-11 Updating the LICENSE
2020-12-11 Starting to update README for v1.3
2020-12-11 Adding a zero-length test to Example9_Lines
2020-12-11 Adding a trap for zero line length
2020-12-11 v1.3: adding support for non-standard I2C and SPI ports
2020-12-11 Updating the library.properties
2020-12-11 Adding a manual reset to Example6 to let an unbranded display be detected
2020-12-13 Adding links to the examples
2021-01-01 Use _delay_ms instead of delay.
    This way it works even if the timers have been changed from the Arduino
    settings.
2021-03-03 Increment version info in libray.json
2021-03-03 v1.3.1
2021-04-02 Each of the fonts can now be included/excluded individually.
2021-04-03 Allow the code to compile and run on MBED (APOLLO3 v2)
2021-04-03 Add note about PROGMEM
2021-04-03 Modify #32 : commenting the #include disables the font
2021-04-03 Disable font 4 by default. Add Example11
2021-04-03 Default to 0x3D
2021-04-03 v1.3.2
2021-04-04 Exclude either by defining or by changing the default.
2021-04-05 Added extra comments. Changed excluded font pointers to NULL
2021-04-06 Templatize class to minimize code size.
    The MicroOLED class is now three different classes for the SPI, I2C, and
    Parallel communication modes, with the functionality in a templatized
    common base class. This avoids always building in the I2C, SPI, and
    Parallel comm code even though only one will likely be used.
    When using SPI mode, this resulted in a hex file using 1092 bytes less,
    not insignificant.
2021-05-08 v1.3.3 - fix compiler warnings
2021-09-01 Add link to hookup guide
    Link in the hookup guide for the Qwiic version
2022-03-09 Add public initDisplay to allow resetting of display's settings in case of corruption.

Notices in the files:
parts and their libraries:
SparkFun-Aesthetics: Licensing: Creative Commons ShareAlike 4.0 International - https://creativecommons.org/licenses/by-sa/4.0
SparkFun-Aesthetics: Released under the Creative Commons Attribution Share-Alike 4.0 License
SparkFun-Aesthetics: https://creativecommons.org/licenses/by-sa/4.0
